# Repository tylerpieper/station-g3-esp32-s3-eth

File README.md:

# Station G3 — Waveshare ESP32-S3-ETH Custom Hardware & Firmware

Hardware design (KiCad interposer) and automated Meshtastic firmware builds for the **B&Q Consulting Station G3** baseboard paired with the **Waveshare ESP32-S3-ETH** (W5500 Wired Ethernet + PoE) module.

Each release automatically compiles upstream [Meshtastic Firmware](https://github.com/meshtastic/firmware) and integrates the custom **Wired Ethernet + BLE Unified OTA Bootloader** from [`tylerpieper/meshtastic-esp32-ethernet-ota`](https://github.com/tylerpieper/meshtastic-esp32-ethernet-ota) into the `app1` (`0x650000`) partition.

---

## Key Features

* **Station G3 High-Power RF Baseboard**: Full support for the primary slot `BQ35LORA900V1M` SX1262 LoRa module (`SX126X_MAX_POWER=19` -> ~31 dBm at PA `PL1`), INA219 telemetry/EEPROM I2C bus, SH1107 128x64 Grove OLED, and Grove UART GPS.
* **Native W5500 10/100Mbps Ethernet (`SPI3_HOST`)**: Dedicated high-speed SPI bus (`GPIO 9..14`) for wired Ethernet + UDP Multicast (`HAS_UDP_MULTICAST=1`) without contending with the LoRa `SPI2_HOST` bus.
* **Full Wired Ethernet + BLE OTA Support (`app1` @ `0x650000`)**:
  * Integrates [`tylerpieper/meshtastic-esp32-ethernet-ota`](https://github.com/tylerpieper/meshtastic-esp32-ethernet-ota) directly into the 16 MB partition layout (`mt-esp32s3-ota.bin`).
  * Includes [`patches/station-g3-eth-ota.patch`](patches/station-g3-eth-ota.patch) so both **DHCP** and **Static IP** configurations (`static_ip`, `static_gw`, `static_mask`, `static_dns`, `eth_enabled`) are seamlessly handed off via NVS to the OTA bootloader and recovered after update.
  * Preserves the ESP32 factory Ethernet MAC address (`ESP_MAC_ETH`) between `app0` and `app1` so DHCP servers assign the exact same IP address during OTA updates.
* **Automated Upstream Tracking & GitHub Releases**:
  * Polls [`meshtastic/firmware`](https://github.com/meshtastic/firmware) every 6 hours and publishes ready-to-flash release bundles on the [GitHub Releases](https://github.com/tylerpieper/station-g3-esp32-s3-eth/releases) page and in [`./builds/INDEX.md`](builds/INDEX.md).

---

## 16 MB Flash Partition Table (`default_16MB.csv`)

| Partition | Flash Offset | Size | Binary Artifact | Purpose |
| :--- | :--- | :--- | :--- | :--- |
| `bootloader` / `partitions` / `boot_app0` | `0x000000` | `64 KB` | *(Inside `.factory.bin` & `.full.bin`)* | Second-stage bootloader, partition table, and OTA data selector |
| `app0` (`ota_0`) | `0x010000` | `6.25 MB` | `firmware-station-g3-waveshare-eth-<ver>.bin` | Primary Meshtastic Firmware (`app0`) |
| `app1` (`ota_1`) | `0x650000` | `6.25 MB` | `mt-esp32s3-ota.bin` | **W5500 Ethernet + BLE Unified OTA Bootloader** ([`meshtastic-esp32-ethernet-ota`](https://github.com/tylerpieper/meshtastic-esp32-ethernet-ota)) |
| `spiffs` | `0xC90000` | `3.375 MB` | `littlefs-station-g3-waveshare-eth-<ver>.bin` | LittleFS Web UI & Filesystem |
| **Combined Full Image** | `0x000000` | `~16 MB` | `firmware-station-g3-waveshare-eth-<ver>.full.bin` | Single-file image with `0x0`, `0x650000` (`app1`), and `0xC90000` (`spiffs`) pre-merged |

---

## Flashing Instructions

### Option 1: Web Flasher (Recommended — No CLI or Tools Required)

You can flash directly from any WebSerial-compatible browser (Google Chrome, Microsoft Edge, Opera, Brave) using our **Custom Meshtastic Web Flasher**:

👉 **[Launch Custom Meshtastic Web Flasher](https://tylerpieper.github.io/Meshtastic-custom-web-flasher/)**

1. Connect the Waveshare ESP32-S3-ETH module to your computer via USB-C.
2. Put the board into bootloader mode: hold down **BOOT**, tap **RESET**, then release **BOOT**.
3. On the Web Flasher, click **Select Device** and choose **Station G3 (Waveshare ESP32-S3-ETH)**.
4. Select the release channel (**Alpha** or **Beta/Stable**) and firmware version.
5. Click **Flash Device** (leave *Full Erase and Install* selected on initial installation so all partitions, including LittleFS and the W5500 Ethernet OTA bootloader, are installed).

---

### Option 2: Command-Line Flashing (Local Tools)

Download the latest release package from the [**GitHub Releases**](https://github.com/tylerpieper/station-g3-esp32-s3-eth/releases) page (`station-g3-waveshare-eth-<version>-<profile>-full-package.zip`, e.g., `vanilla` or `pr-10531_-_Multi_MQTT`) or grab the `.full.bin` directly from [`builds/`](builds/INDEX.md).

#### Initial Full Flash (Erases Flash & Installs All Partitions)

Put the Waveshare ESP32-S3-ETH into USB bootloader mode (hold **BOOT**, tap **RESET**, release **BOOT**).

##### Method A: Automated Script (Recommended)
```bash
# Linux / macOS:
./device-install.sh -p /dev/ttyACM0 -f firmware-station-g3-waveshare-eth-<version>.factory.bin

# Windows (PowerShell / CMD):
.\device-install.bat -p COM3 -f firmware-station-g3-waveshare-eth-<version>.factory.bin
```

##### Method B: Single-File All-in-One Merged Flash (`.full.bin`)
Flash the single pre-merged 16 MB binary at offset `0x0`:
```bash
python -m esptool --chip esp32s3 --port <PORT> erase-flash
python -m esptool --chip esp32s3 --port <PORT> write-flash 0x0 firmware-station-g3-waveshare-eth-<version>.full.bin
```

##### Method C: Manual Multi-Partition `esptool` Flash
```bash
python -m esptool --chip esp32s3 --port <PORT> erase-flash
python -m esptool --chip esp32s3 --port <PORT> write-flash \
  0x000000 firmware-station-g3-waveshare-eth-<version>.factory.bin \
  0x650000 mt-esp32s3-ota.bin \
  0xC90000 littlefs-station-g3-waveshare-eth-<version>.bin
```

---

### Subsequent Firmware Updates (Preserves Settings)

#### Over Wired Ethernet (OTA — No USB Required)
Once `mt-esp32s3-ota.bin` is installed in `app1` (`0x650000`), you can update the node remotely over Ethernet (TCP port `3232`) using the Meshtastic CLI:
```bash
meshtastic --host <DEVICE_IP> --ota-update firmware-station-g3-waveshare-eth-<version>.bin
```

#### Over USB Serial (`device-update`)
```bash
# Linux / macOS:
./device-update.sh -p /dev/ttyACM0 -f firmware-station-g3-waveshare-eth-<version>.bin

# Windows:
.\device-update.bat -p COM3 -f firmware-station-g3-waveshare-eth-<version>.bin
```

---

## Repository Structure

* [`MeshCore/`](MeshCore/README.md) — Self-contained MeshCore variant definition, build guide, and pre-built merged binaries for all roles.
* [`meshtastic_migration.md`](meshtastic_migration.md) — Step-by-step migration guide for switching from the stock `BQESP32V1M` MCU to the Waveshare module while preserving your configuration.
* [`hardware/`](hardware/README.md) — KiCad schematic, PCB layout, and Gerber fabrication files for the Station G3 Waveshare ESP32-S3-ETH interposer.
* [`variants/esp32s3/station-g3-waveshare-eth/`](variants/esp32s3/station-g3-waveshare-eth/) — Custom PlatformIO environment, pin definitions, and fallback `mt-esp32s3-ota.bin`.
* [`patches/`](patches/) — Firmware patches including [`station-g3-eth-ota.patch`](patches/station-g3-eth-ota.patch) for Static IP + Ethernet NVS OTA handoff.
* [`build-config.yaml`](build-config.yaml) — Release channel tracking and build profile configuration.
* [`builds/`](builds/INDEX.md) — Automatically maintained index and artifacts for active Alpha and Beta releases.

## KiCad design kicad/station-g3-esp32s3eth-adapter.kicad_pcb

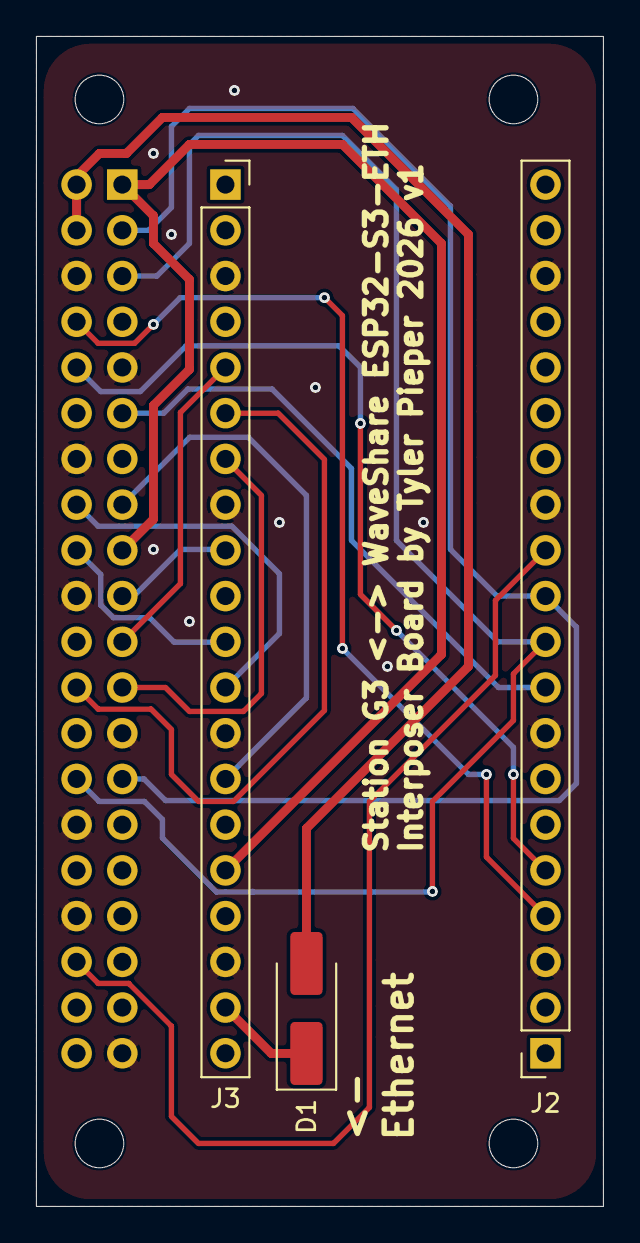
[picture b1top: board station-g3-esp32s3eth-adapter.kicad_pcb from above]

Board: 2 copper layers, 31.5 x 65.0 mm, 4 parts (1 on the bottom side), 17 nets.

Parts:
D1: D_Schottky; D_SMA_Handsoldering
J1: Station G3 20pin; PinHeader_2x20_P2.54mm_Vertical
J2: Waveshare Upper; PinSocket_1x20_P2.54mm_Vertical
J3: Waveshare Lower; PinSocket_1x20_P2.54mm_Vertical

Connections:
/3V3_LOGIC: J1.1, J1.17, J3.36
/5V_ESP_IN: D1.1 (K), J3.39
/5V_VSYS: D1.2 (A), J1.2, J1.4
/GND: J1.6, J1.9, J1.14, J1.20, J1.25, J1.30, J1.34, J1.39, J2.3, J2.8, J2.13, J2.18, J3.23, J3.28, J3.33, J3.38
/I2C_SCL: J1.5, J1.28, J2.10
/I2C_SDA: J1.3, J1.27, J2.11
/LNA_MODE: J1.16, J3.32
/LORA_BUSY: J1.18, J3.31
/LORA_CS: J1.24, J3.26
/LORA_DIO1: J1.15, J3.34
/LORA_MISO: J1.21, J3.25
/LORA_MOSI: J1.19, J3.29
/LORA_RST: J1.36, J2.12
/LORA_SCK: J1.23, J3.27
/PA_ENABLE: J1.11, J2.9
/UART_RX: J1.10, J2.5
/UART_TX: J1.8, J2.4

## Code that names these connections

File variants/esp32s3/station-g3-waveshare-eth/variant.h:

#pragma once

// ============================================================================
// Station G3 + Waveshare ESP32-S3-ETH Custom Interposer (Rev 1.0)
// ============================================================================

// 1. I2C Bus (Grove OLED + Station G3 INA219/EEPROM on J1 Pins 3, 5, 27, 28)
#define USE_SH1107_128_64
#define I2C_SDA 40 // J2 Pin 11 (GPIO40) <- J1 Pins 3 & 27 (I2C SDA / EEPROM SDA)
#define I2C_SCL 41 // J2 Pin 10 (GPIO41) <- J1 Pins 5 & 28 (I2C SCL / EEPROM SCL)

// 2. Grove UART / GPS Header (J1 Pins 8 & 10)
#define HAS_GPS 1
#define GPS_TX_PIN 48 // J2 Pin 4 (GPIO48) <- J1 Pin 8  (UART TX)
#define GPS_RX_PIN 47 // J2 Pin 5 (GPIO47) <- J1 Pin 10 (UART RX)

// 3. User Button & Onboard WS2812 RGB Status LED (Waveshare ESP32-S3-ETH)
#define BUTTON_PIN 0 // Waveshare onboard BOOT button (GPIO0)
#define BUTTON_NEED_PULLUP

#define HAS_NEOPIXEL 1
#define NEOPIXEL_COUNT 1
#define NEOPIXEL_DATA 21 // Waveshare onboard WS2812 RGB LED (GPIO21)
#define NEOPIXEL_TYPE (NEO_GRB + NEO_KHZ800)

// 4. Station G3 Primary Slot SX1262 LoRa Radio (BQ35LORA900V1M)
#define USE_SX1262
#define LORA_MISO 1   // J3 Pin 25 (GPIO1)  <- J1 Pin 21 (Primary Slot MISO)
#define LORA_CS 2     // J3 Pin 26 (GPIO2)  <- J1 Pin 24 (Primary Slot NSS)
#define LORA_SCK 3    // J3 Pin 27 (GPIO3)  <- J1 Pin 23 (Primary Slot SCK)
#define LORA_MOSI 15  // J3 Pin 29 (GPIO15) <- J1 Pin 19 (Primary Slot MOSI)
#define LORA_RESET 39 // J2 Pin 12 (GPIO39) <- J1 Pin 36 (Primary Slot NRESET)
#define LORA_DIO1 17  // J3 Pin 34 (GPIO17) <- J1 Pin 15 (Primary Slot DIO1)

#ifdef USE_SX1262
#define SX126X_CS LORA_CS
#define SX126X_DIO1 LORA_DIO1
#define SX126X_BUSY 18 // J3 Pin 31 (GPIO18) <- J1 Pin 18 (Primary Slot BUSY)
#define SX126X_RESET LORA_RESET
#define SX126X_DIO2_AS_RF_SWITCH
#define SX126X_DIO3_TCXO_VOLTAGE 1.8

// Station G3 BQ35LORA900V1M PA cap (19 dBm SX1262 drive -> ~31 dBm out at PA PL1)
#define SX126X_MAX_POWER 19
#endif

// Station G3 Baseboard PA/LNA header pins (controlled by hardware jumpers PA-PL1/PL2 & LNA-P by default)
#define LORA_PA_MODE_PIN 42  // J2 Pin 9  (GPIO42) <- J1 Pin 11 (PA Mode)
#define LORA_LNA_MODE_PIN 16 // J3 Pin 32 (GPIO16) <- J1 Pin 16 (Primary Slot LNA Mode)
#define LORA_STATION_G3_LNA_EN LORA_LNA_MODE_PIN

// 5. Waveshare Onboard W5500 10/100Mbps Ethernet (Internal SPI3_HOST Routing)
#define HAS_ETHERNET 1
#define USE_WS5500 1 // Uses ESP-IDF native W5500 driver in WiFiAPClient.cpp

#define ETH_MOSI_PIN 11
#define ETH_MISO_PIN 12
#define ETH_SCLK_PIN 13
#define ETH_CS_PIN 14
#define ETH_INT_PIN 10
#define ETH_RST_PIN 9
#define ETH_ADDR 1
